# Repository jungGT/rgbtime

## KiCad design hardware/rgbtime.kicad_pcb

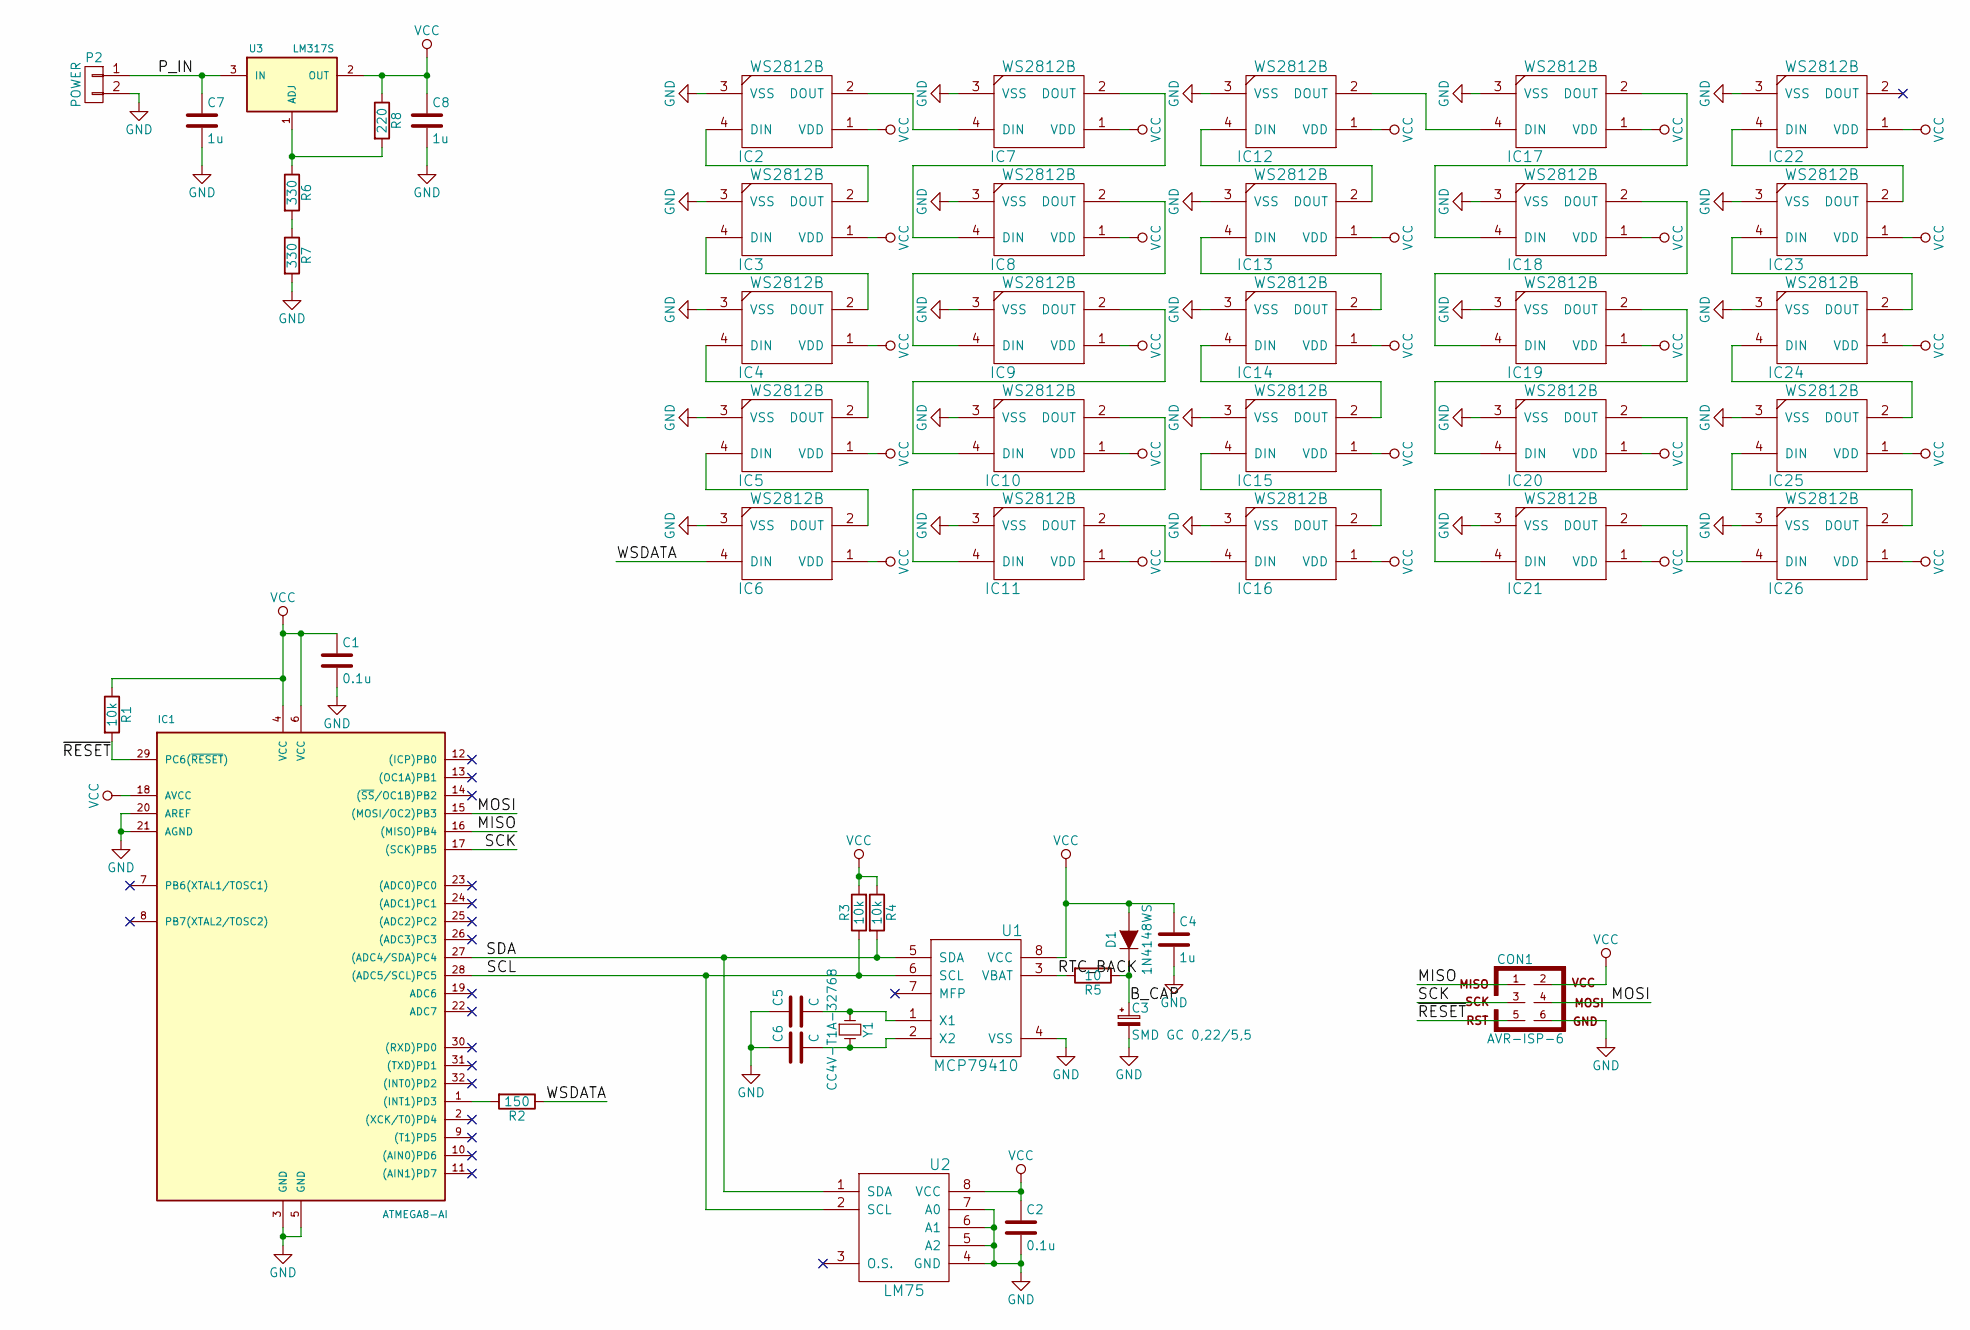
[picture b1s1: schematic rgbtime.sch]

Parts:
C1, C2: 0.1u; C_0603_HandSoldering
C3: SMD GC 0,22/5,5; c_elec_8x10.5
C4, C7, C8: 1u; C_0805_HandSoldering
C5, C6: C; C_0603_HandSoldering
CON1: AVR-ISP-6; Pin_Header_Straight_2x03
D1: 1N4148WS; SOD-323
IC1: ATMEGA8-AI; TQFP-32_7x7mm_Pitch0.8mm
IC2, IC3, IC4, IC5, IC6, IC7, IC8, IC9, IC10, IC11, IC12, IC13, IC14, IC15, IC16, IC17, IC18, IC19, IC20, IC21, IC22, IC23, IC24, IC25, IC26: WS2812B
P2: POWER; bornier2
R1, R3, R4: 10k; R_0603_HandSoldering
R2: 150; R_0603_HandSoldering
R5: 10; R_0603_HandSoldering
R6, R7: 330; R_0603_HandSoldering
R8: 220; R_0603_HandSoldering
U1: MCP79410; SO8
U2: LM75; SO8
U3: LM317S; TO-263
Y1: CC4V-T1A-32768; CC4V-T1A

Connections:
/B_CAP: C3.1, D1.1 (K), R5.1
/LM75_ALM: IC1.32 ((INT0)PD2), U2.3 (O.S.)
/MISO: CON1.1, IC1.16 ((MISO)PB4)
/MOSI: CON1.4, IC1.15 ((MOSI/OC2)PB3)
/P_IN: C7.1, P2.1, U3.3 (IN)
/RTC_ALM: IC1.26 ((ADC3)PC3), U1.7 (MFP)
/RTC_BACK: R5.2, U1.3 (VBAT)
/SCK: CON1.3, IC1.17 ((SCK)PB5)
/SCL: IC1.28 ((ADC5/SCL)PC5), R3.1, U1.6 (SCL), U2.2 (SCL)
/SDA: IC1.27 ((ADC4/SDA)PC4), R4.2, U1.5 (SDA), U2.1 (SDA)
/WSDATA: IC6.4 (DIN), R2.1
/~RESET: CON1.5, IC1.29 (PC6(~RESET~)), R1.2
GND: C1.2, C2.2, C3.2, C4.2, C5.1, C6.1, C7.2, C8.2, CON1.6, IC1.3 (GND), IC1.5 (GND), IC1.20 (AREF), IC1.21 (AGND), IC2.3 (VSS), IC3.3 (VSS), IC4.3 (VSS), IC5.3 (VSS), IC6.3 (VSS), IC7.3 (VSS), IC8.3 (VSS), IC9.3 (VSS), IC10.3 (VSS), IC11.3 (VSS), IC12.3 (VSS), IC13.3 (VSS), IC14.3 (VSS), IC15.3 (VSS), IC16.3 (VSS), IC17.3 (VSS), IC18.3 (VSS), IC19.3 (VSS), IC20.3 (VSS), IC21.3 (VSS), IC22.3 (VSS), IC23.3 (VSS), IC24.3 (VSS), IC25.3 (VSS), IC26.3 (VSS), P2.2, R7.2, U1.4 (VSS), U2.4 (GND), U2.5 (A2), U2.6 (A1), U2.7 (A0)
unnamed: C5.2, U1.1 (X1), Y1.1
unnamed: C6.2, U1.2 (X2), Y1.2
unnamed: IC1.1 ((INT1)PD3), R2.2
unnamed: IC2.2 (DOUT), IC7.4 (DIN)
unnamed: IC2.4 (DIN), IC3.2 (DOUT)
unnamed: IC3.4 (DIN), IC4.2 (DOUT)
unnamed: IC4.4 (DIN), IC5.2 (DOUT)
unnamed: IC5.4 (DIN), IC6.2 (DOUT)
unnamed: IC7.2 (DOUT), IC8.4 (DIN)
unnamed: IC8.2 (DOUT), IC9.4 (DIN)
unnamed: IC10.2 (DOUT), IC11.4 (DIN)
unnamed: IC9.2 (DOUT), IC10.4 (DIN)
unnamed: IC11.2 (DOUT), IC16.4 (DIN)
unnamed: IC12.2 (DOUT), IC17.4 (DIN)
unnamed: IC12.4 (DIN), IC13.2 (DOUT)
unnamed: IC13.4 (DIN), IC14.2 (DOUT)
unnamed: IC14.4 (DIN), IC15.2 (DOUT)
unnamed: IC15.4 (DIN), IC16.2 (DOUT)
unnamed: IC17.2 (DOUT), IC18.4 (DIN)
unnamed: IC18.2 (DOUT), IC19.4 (DIN)
unnamed: IC19.2 (DOUT), IC20.4 (DIN)
unnamed: IC20.2 (DOUT), IC21.4 (DIN)
unnamed: IC21.2 (DOUT), IC26.4 (DIN)
unnamed: IC22.4 (DIN), IC23.2 (DOUT)
unnamed: IC23.4 (DIN), IC24.2 (DOUT)
unnamed: IC24.4 (DIN), IC25.2 (DOUT)
unnamed: IC25.4 (DIN), IC26.2 (DOUT)
unnamed: R6.1, R8.2, U3.1 (ADJ)
unnamed: R6.2, R7.1
VCC: C1.1, C2.1, C4.1, C8.1, CON1.2, D1.2 (A), IC1.4 (VCC), IC1.6 (VCC), IC1.18 (AVCC), IC2.1 (VDD), IC3.1 (VDD), IC4.1 (VDD), IC5.1 (VDD), IC6.1 (VDD), IC7.1 (VDD), IC8.1 (VDD), IC9.1 (VDD), IC10.1 (VDD), IC11.1 (VDD), IC12.1 (VDD), IC13.1 (VDD), IC14.1 (VDD), IC15.1 (VDD), IC16.1 (VDD), IC17.1 (VDD), IC18.1 (VDD), IC19.1 (VDD), IC20.1 (VDD), IC21.1 (VDD), IC22.1 (VDD), IC23.1 (VDD), IC24.1 (VDD), IC25.1 (VDD), IC26.1 (VDD), R1.1, R3.2, R4.1, R8.1, U1.8 (VCC), U2.8 (VCC), U3.2 (OUT)

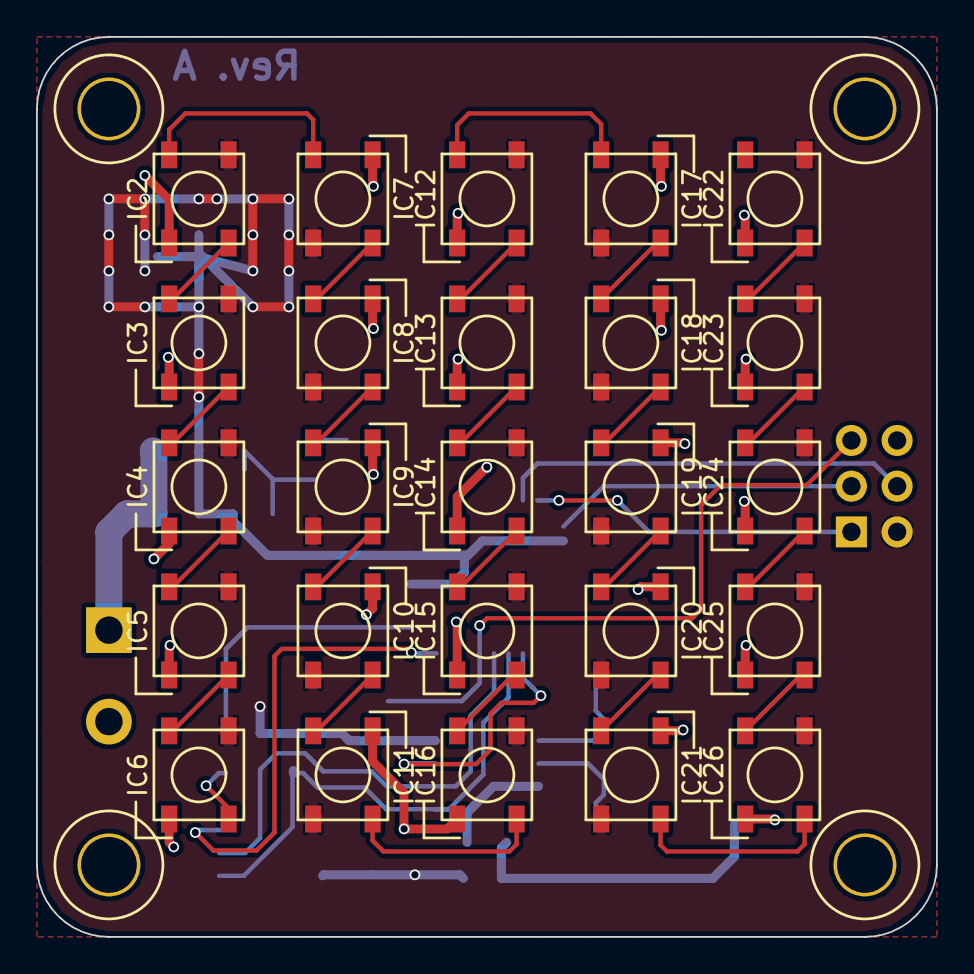
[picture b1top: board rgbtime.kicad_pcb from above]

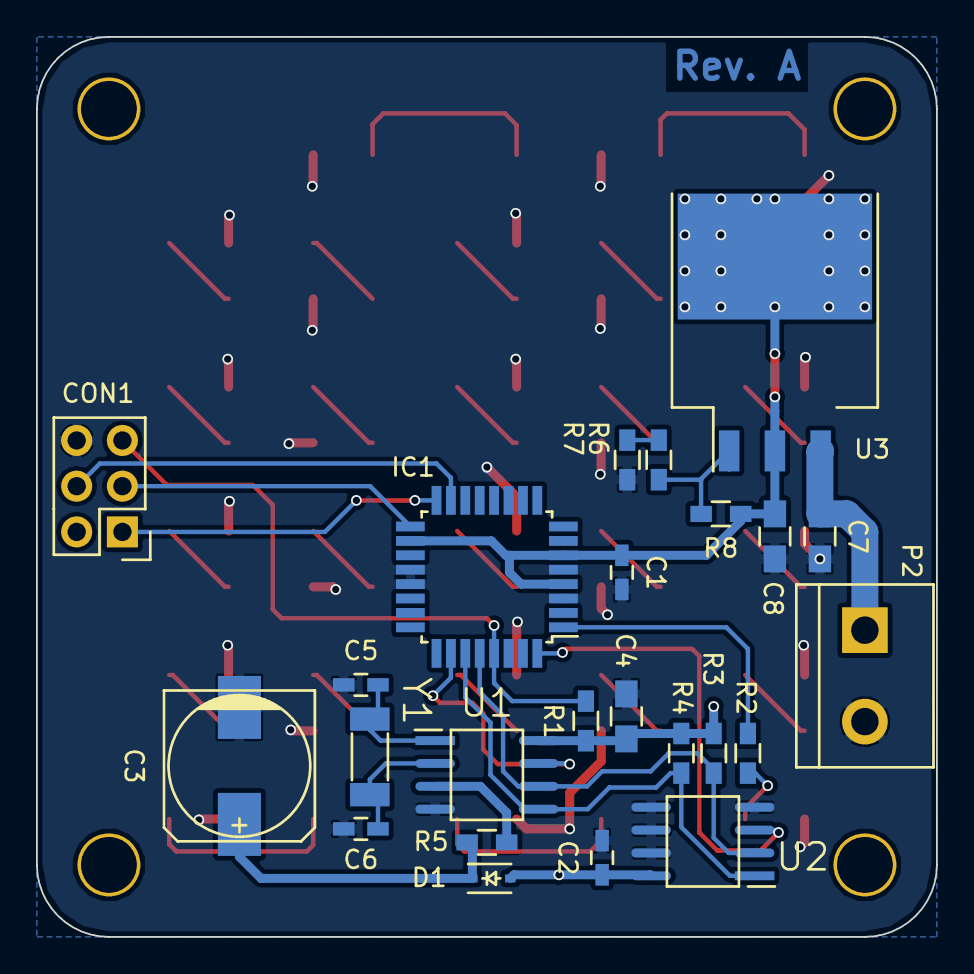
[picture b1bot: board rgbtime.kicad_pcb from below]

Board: 2 copper layers, 50.0 x 50.0 mm, 49 parts (24 on the bottom side), 43 nets.

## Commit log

2015-07-09 initial commit, missing USB footprint
2015-07-09 started layout, matrix placed, need USB footprint
2015-07-10 restructured repo
2015-07-10 added firmware
2015-07-11 added LM75 temperature sensor readout
2015-07-12 fixed signed int cast
2015-07-12 added rtc library
2015-07-12 final hardware revision A done, sent to fab
2015-07-13 minimal RTC code functionality, LM75 needs more work
2015-07-19 moved ws2812 routines to separate lib
2015-08-21 fixed timing, new color lookup
2015-08-22 added rudimentary digit drawing and canvas to hardware mapping
2015-08-29 added more convenient register access functions as they are very commonly used
2015-08-29 fixed time reset issues
2015-09-02 added correct time display and set initial time
2015-09-06 changed initial time
